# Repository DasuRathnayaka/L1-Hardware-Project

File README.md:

# Automated Camera Stand
## What is this?
This is an Automated camera stand which possible to guide using GPS coordinates with an obstacle avoidance navigation system. This is made to help wildlife photographers to take good photographs in insecure environments.

## Why is this?
We mainly focused on avoiding danger for the wildlife photographer and the safety of the camera. In this period many wildlife photographers are facing danger while taking photos due to animal attacks. We are going to introduce a new device to avoid such a problem.

## 3D Model

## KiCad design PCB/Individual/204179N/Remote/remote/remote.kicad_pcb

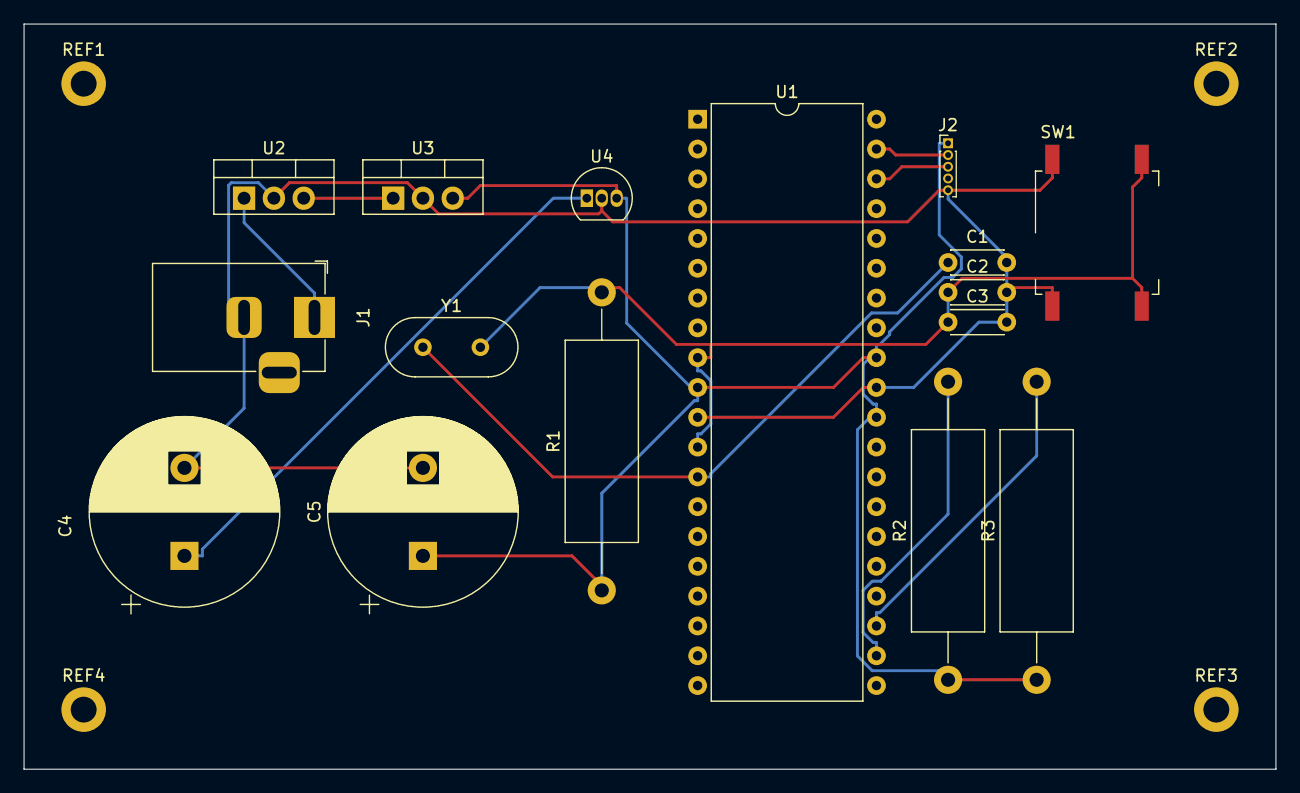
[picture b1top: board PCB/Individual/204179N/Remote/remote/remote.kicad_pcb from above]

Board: 2 copper layers, 106.7 x 63.5 mm, 20 parts (0 on the bottom side), 11 nets.

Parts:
C1, C2: 22pF; C_Disc_D4.3mm_W1.9mm_P5.00mm
C3: 10uF; C_Disc_D4.3mm_W1.9mm_P5.00mm
C4, C5: 470uF; CP_Radial_D16.0mm_P7.50mm
J1: Barrel_Jack; BarrelJack_Horizontal
J2: Joystick (Motor); PinHeader_1x05_P1.00mm_Vertical
R1: 10k; R_Axial_DIN0617_L17.0mm_D6.0mm_P25.40mm_Horizontal
R2, R3: 4.7k; R_Axial_DIN0617_L17.0mm_D6.0mm_P25.40mm_Horizontal
REF1: M1; MountingHole_2.2mm_M2_ISO14580_Pad
REF2: M2; MountingHole_2.2mm_M2_ISO14580_Pad
REF3: M3; MountingHole_2.2mm_M2_ISO14580_Pad
REF4: M4; MountingHole_2.2mm_M2_ISO14580_Pad
SW1: Reset Button; SW_MEC_5GSH9
U1: ATmega32-16P; DIP-40_W15.24mm
U2: L7809; TO-220-3_Vertical
U3: L7805; TO-220-3_Vertical
U4: L78L33_TO92; TO-92_Inline
Y1: Crystal; Crystal_HC18-U_Vertical

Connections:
/Atmega32/5V: C5.1, J2.1 (5V), R1.1, R2.1, R3.1, U1.10 (VCC), U1.30 (AVCC), U1.32 (AREF), U3.3 (OUT), U4.3 (VI)
/Atmega32/A1: J2.2 (VRx), U1.39 (PA1)
/Atmega32/A2: J2.3 (VRy), U1.38 (PA2)
/Atmega32/GND: C1.2, C2.2, C3.2, C4.2, C5.2, J1.2, J2.5 (GND), SW1.1 (A), SW1.2 (A), U1.11 (GND), U1.31 (GND), U2.2 (GND), U3.2 (GND), U4.2 (GND)
/Atmega32/SCL: R2.2, U1.22 (PC0)
/Atmega32/SDA: R3.2, U1.23 (PC1)
/Power Supply/3.3V: C4.1, U4.1 (VO)
/Power Supply/12V: J1.1, U2.1 (IN)
unnamed: C1.1, U1.13 (XTAL1), Y1.1
unnamed: C2.1, C3.1, R1.2, SW1.3 (B), SW1.4 (B), U1.9 (~RESET), U1.12 (XTAL2), Y1.2
unnamed: U2.3 (OUT), U3.1 (IN)

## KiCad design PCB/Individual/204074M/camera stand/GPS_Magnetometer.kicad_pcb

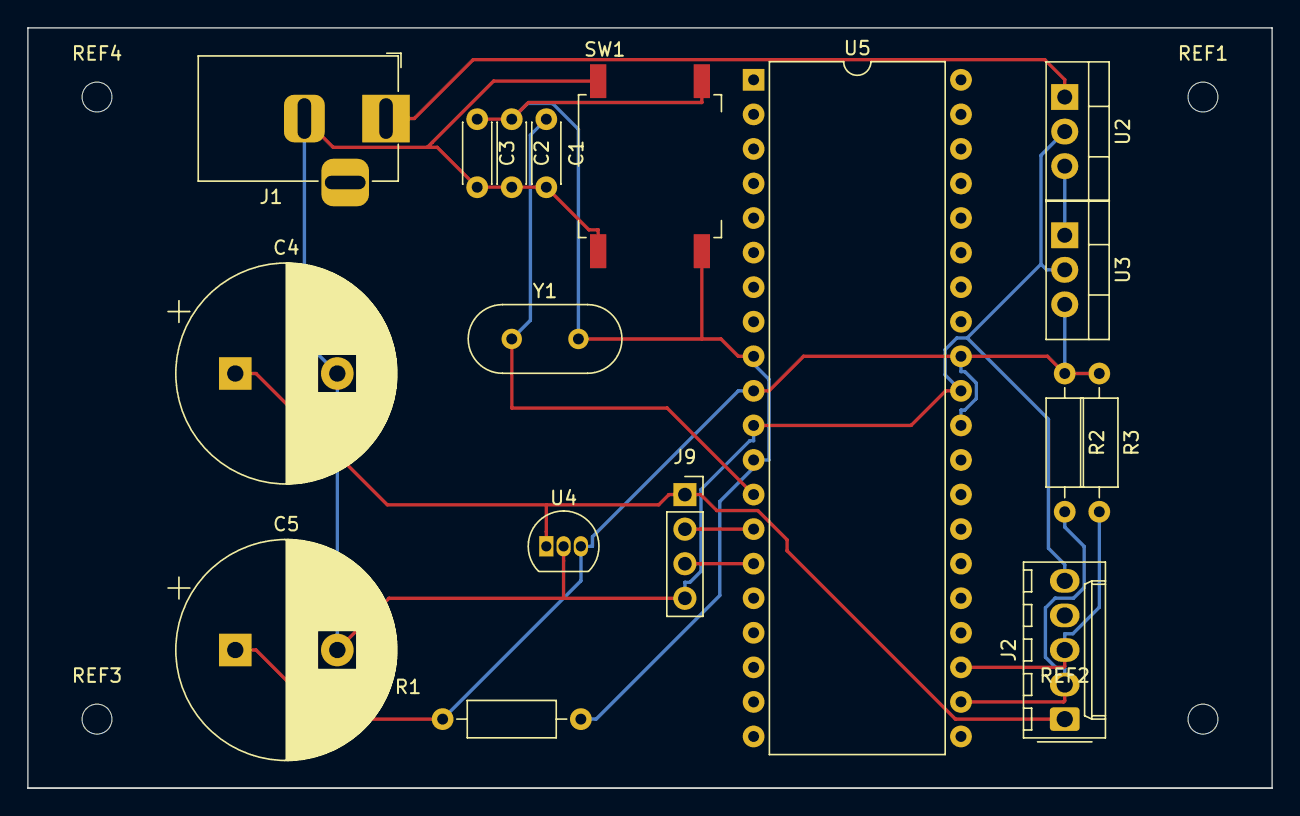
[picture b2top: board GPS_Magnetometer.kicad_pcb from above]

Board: 2 copper layers, 91.4 x 55.9 mm, 21 parts (0 on the bottom side), 11 nets.

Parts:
C1, C2: 22pF; C_Disc_D4.3mm_W1.9mm_P5.00mm
C3: 10uF; C_Disc_D4.3mm_W1.9mm_P5.00mm
C4, C5: 470uF; CP_Radial_D16.0mm_P7.50mm
J1: Barrel_Jack; BarrelJack_Horizontal
J2: HMC5883L; Molex_KK-254_AE-6410-05A_1x05_P2.54mm_Vertical
J9: GPS Module; PinSocket_1x04_P2.54mm_Vertical
R1: 10k; R_Axial_DIN0207_L6.3mm_D2.5mm_P10.16mm_Horizontal
R2, R3: 4.7k; R_Axial_DIN0207_L6.3mm_D2.5mm_P10.16mm_Horizontal
REF1, REF2, REF3, REF4: MountingHole_2.2mm_M2
SW1: Reset Button; SW_MEC_5GSH9
U2: L7809; TO-220-3_Vertical
U3: L7805; TO-220-3_Vertical
U4: L78L33_TO92; TO-92_Inline
U5: ATmega32-16P; DIP-40_W15.24mm
Y1: Crystal; Crystal_HC18-U_Vertical

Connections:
/Atmega32/5V: C5.1, R1.1, R2.1, R3.1, U3.3 (OUT), U4.3 (VI), U5.10 (VCC), U5.30 (AVCC), U5.32 (AREF)
/Atmega32/GND: C1.2, C2.2, C3.2, C4.2, C5.2, J1.2, J2.5 (GND), J9.4 (GND), SW1.1 (A), SW1.2 (A), U2.2 (GND), U3.2 (GND), U4.2 (GND), U5.11 (GND), U5.31 (GND)
/Atmega32/Rx: J9.2 (Tx), U5.14 (PD0)
/Atmega32/SCL: J2.2 (SCL), R2.2, U5.22 (PC0)
/Atmega32/SDA: J2.3 (SDA), R3.2, U5.23 (PC1)
/Atmega32/Tx: J9.3 (Rx), U5.15 (PD1)
/Power Supply/3.3V: C4.1, J2.1 (VCC), J9.1 (VCC), U4.1 (VO)
/Power Supply/12V: J1.1, U2.1 (IN)
unnamed: C1.1, U5.13 (XTAL1), Y1.1
unnamed: C2.1, C3.1, R1.2, SW1.3 (B), SW1.4 (B), U5.9 (~RESET), U5.12 (XTAL2), Y1.2
unnamed: U2.3 (OUT), U3.1 (IN)

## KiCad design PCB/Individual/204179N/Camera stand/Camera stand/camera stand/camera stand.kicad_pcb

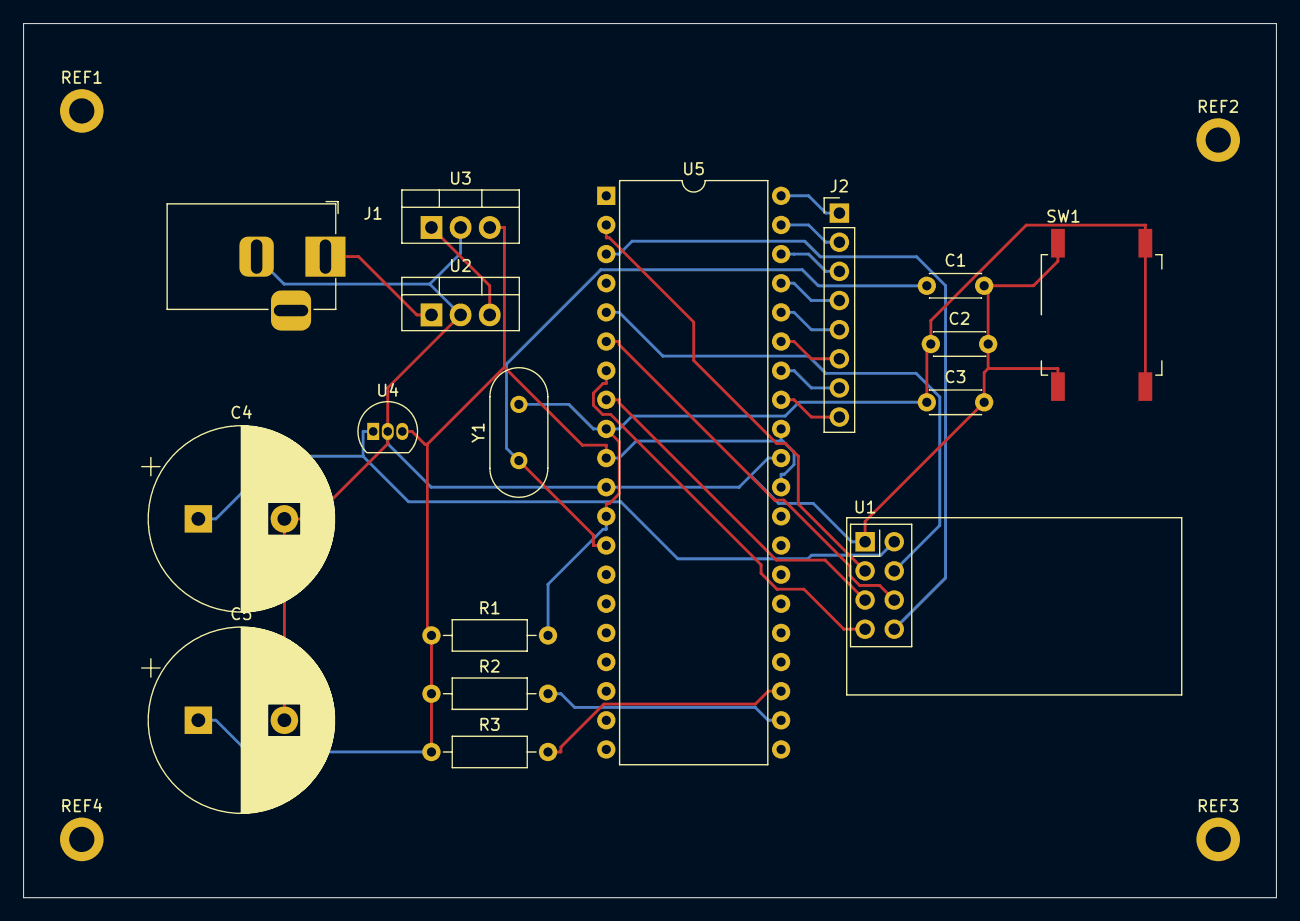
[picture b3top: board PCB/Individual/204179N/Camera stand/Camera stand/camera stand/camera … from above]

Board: 2 copper layers, 109.2 x 76.2 mm, 21 parts (0 on the bottom side), 23 nets.

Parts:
C1, C2: 22pF; C_Disc_D4.3mm_W1.9mm_P5.00mm
C3: 10uF; C_Disc_D4.3mm_W1.9mm_P5.00mm
C4, C5: 470uF; CP_Radial_D16.0mm_P7.50mm
J1: Barrel_Jack; BarrelJack_Horizontal
J2: Keypad 4x4; PinHeader_1x08_P2.54mm_Vertical
R1: 10k; R_Axial_DIN0207_L6.3mm_D2.5mm_P10.16mm_Horizontal
R2, R3: 4.7k; R_Axial_DIN0207_L6.3mm_D2.5mm_P10.16mm_Horizontal
REF1: M1; MountingHole_2.2mm_M2_ISO14580_Pad
REF2: M2; MountingHole_2.2mm_M2_ISO14580_Pad
REF3: M3; MountingHole_2.2mm_M2_ISO14580_Pad
REF4: M4; MountingHole_2.2mm_M2_ISO14580_Pad
SW1: Reset Button; SW_MEC_5GSH9
U1: NRF24L01; nRF24L01_Breakout
U2: L7809; TO-220-3_Vertical
U3: L7805; TO-220-3_Vertical
U4: L78L33_TO92; TO-92_Inline
U5: ATmega32-16P; DIP-40_W15.24mm
Y1: Crystal; Crystal_HC18-U_Vertical

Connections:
/Atmega32/5V: C5.1, R1.1, R2.1, R3.1, U3.3 (OUT), U4.3 (VI), U5.10 (VCC), U5.30 (AVCC), U5.32 (AREF)
/Atmega32/A0: J2.1 (Col_A), U5.40 (PA0)
/Atmega32/A1: J2.2 (Col_B), U5.39 (PA1)
/Atmega32/A2: J2.3 (Col_C), U5.38 (PA2)
/Atmega32/A3: J2.4 (Col_D), U5.37 (PA3)
/Atmega32/A4: J2.5 (Row_1), U5.36 (PA4)
/Atmega32/A5: J2.6 (Row_2), U5.35 (PA5)
/Atmega32/A6: J2.7 (Row_3), U5.34 (PA6)
/Atmega32/A7: J2.8 (Row_4), U5.33 (PA7)
/Atmega32/CE: U1.3 (CE), U5.2 (PB1)
/Atmega32/CSN: U1.4 (~CSN), U5.5 (PB4)
/Atmega32/GND: C1.2, C2.2, C3.2, C4.2, C5.2, J1.2, SW1.1 (A), SW1.2 (A), U1.1 (GND), U2.2 (GND), U3.2 (GND), U4.2 (GND), U5.11 (GND), U5.31 (GND)
/Atmega32/IRQ: U1.8 (IRQ), U5.3 (PB2)
/Atmega32/MISO: U1.7 (MISO), U5.7 (PB6)
/Atmega32/MOSI: U1.6 (MOSI), U5.6 (PB5)
/Atmega32/SCK: U1.5 (SCK), U5.8 (PB7)
/Atmega32/SCL: R2.2, U5.22 (PC0)
/Atmega32/SDA: R3.2, U5.23 (PC1)
/Power Supply/3.3V: C4.1, U1.2 (VCC), U4.1 (VO)
/Power Supply/12V: J1.1, U2.1 (IN)
unnamed: C1.1, U5.13 (XTAL1), Y1.1
unnamed: C2.1, C3.1, R1.2, SW1.3 (B), SW1.4 (B), U5.9 (~RESET), U5.12 (XTAL2), Y1.2
unnamed: U2.3 (OUT), U3.1 (IN)

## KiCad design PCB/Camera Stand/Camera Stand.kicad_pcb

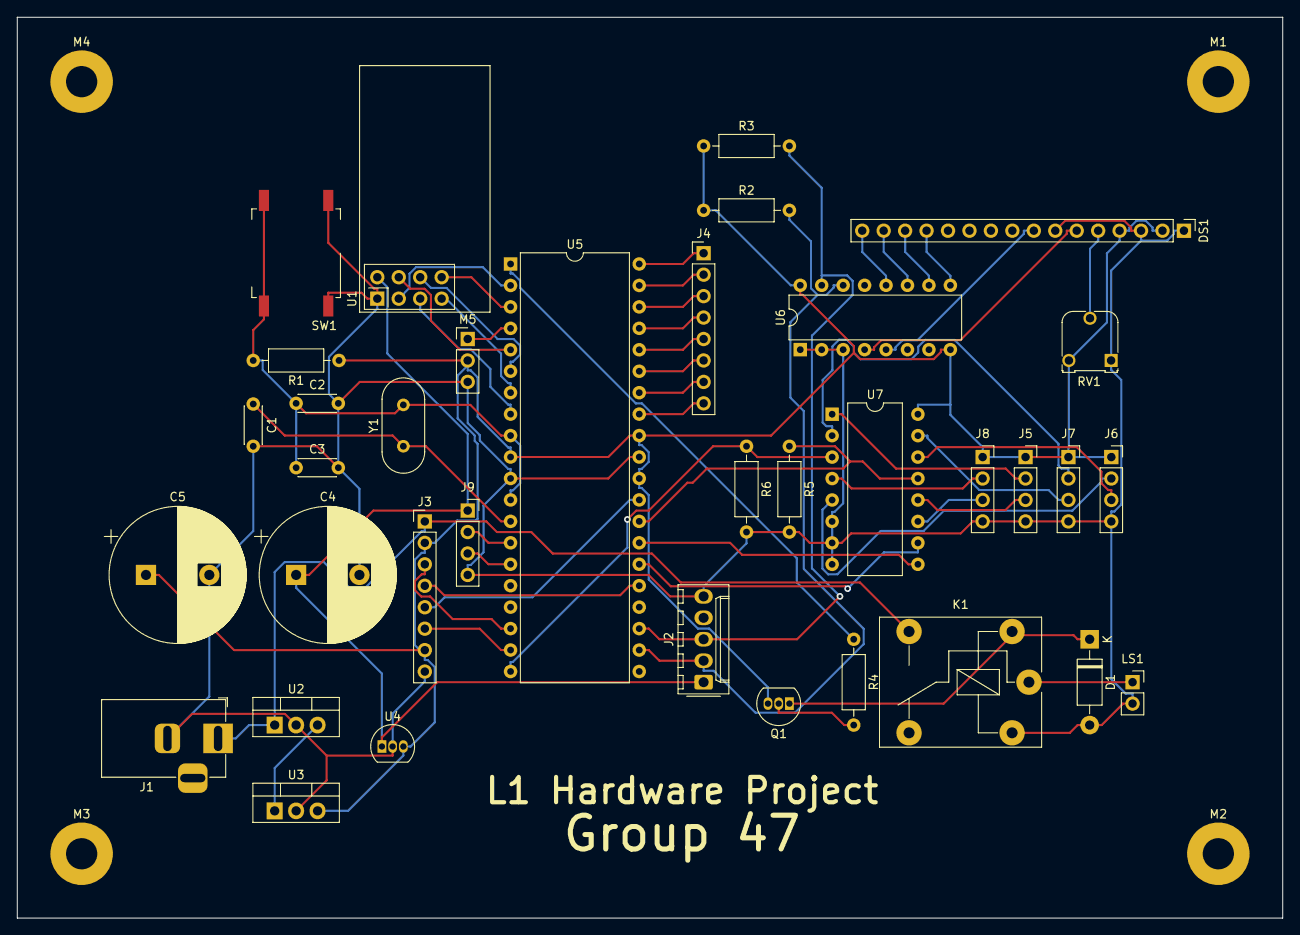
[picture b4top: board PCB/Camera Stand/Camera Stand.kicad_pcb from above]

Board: 2 copper layers, 149.9 x 106.7 mm, 40 parts (0 on the bottom side), 53 nets.

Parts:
C1, C2: 22pF; C_Disc_D4.3mm_W1.9mm_P5.00mm
C3: 10uF; C_Disc_D4.3mm_W1.9mm_P5.00mm
C4, C5: 470uF; CP_Radial_D16.0mm_P7.50mm
D1: 1N4007; D_DO-41_SOD81_P10.16mm_Horizontal
DS1: HY1602E; PinHeader_1x16_P2.54mm_Vertical
J1: Barrel_Jack; BarrelJack_Horizontal
J2: HMC5883L; Molex_KK-254_AE-6410-05A_1x05_P2.54mm_Vertical
J3: Motor Drive; PinHeader_1x08_P2.54mm_Vertical
J4: Keypad 4x4; PinHeader_1x08_P2.54mm_Vertical
J5: Ultrasonic Left Front; PinSocket_1x04_P2.54mm_Vertical
J6: Ultrasonic Right Front; PinSocket_1x04_P2.54mm_Vertical
J7: Ultrasonic Left Back; PinSocket_1x04_P2.54mm_Vertical
J8: Ultrasonic Right Back; PinSocket_1x04_P2.54mm_Vertical
J9: GPS Module; PinSocket_1x04_P2.54mm_Vertical
K1: Relay; Relay_SPDT_Finder_36.11
LS1: Speaker; PinSocket_1x02_P2.54mm_Vertical
M1, M2, M3, M4: MountingHole_3.7mm_Pad
M5: Motor_Servo; PinHeader_1x03_P2.54mm_Vertical
Q1: PN2222A; TO-92_Inline
R1, R5, R6: 10k; R_Axial_DIN0207_L6.3mm_D2.5mm_P10.16mm_Horizontal
R2, R3: 4.7k; R_Axial_DIN0207_L6.3mm_D2.5mm_P10.16mm_Horizontal
R4: 100k; R_Axial_DIN0207_L6.3mm_D2.5mm_P10.16mm_Horizontal
RV1: Potentiometer; Potentiometer_Runtron_RM-065_Vertical
SW1: Reset Button; SW_MEC_5GSH9
U1: NRF24L01; nRF24L01_Breakout
U2: L7809; TO-220-3_Vertical
U3: L7805; TO-220-3_Vertical
U4: L78L33_TO92; TO-92_Inline
U5: ATmega32-16P; DIP-40_W15.24mm
U6: PCF8574A; DIP-16_W7.62mm
U7: CD4052B; DIP-16_W10.16mm
Y1: Crystal; Crystal_HC18-U_Vertical

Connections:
/Atmega32/5V: C5.1, DS1.2 (LEDA), DS1.4 (VDD), J3.2 (ENA), J3.7 (ENB), J5.1 (VCC), J6.1 (VCC), J7.1 (VCC), J8.1 (VCC), M5.2 (+), Q1.3 (C), R1.1, R2.1, R3.1, RV1.3, U3.3 (OUT), U4.3 (VI), U5.10 (VCC), U5.30 (AVCC), U5.32 (AREF), U6.8 (VSS), U6.16 (VDD), U7.16 (VDD)
/Atmega32/A0: J4.1 (Col_A), U5.40 (PA0)
/Atmega32/A1: J4.2 (Col_B), U5.39 (PA1)
/Atmega32/A2: J4.3 (Col_C), U5.38 (PA2)
/Atmega32/A3: J4.4 (Col_D), U5.37 (PA3)
/Atmega32/A4: J4.5 (Row_1), U5.36 (PA4)
/Atmega32/A5: J4.6 (Row_2), U5.35 (PA5)
/Atmega32/A6: J4.7 (Row_3), U5.34 (PA6)
/Atmega32/A7: J4.8 (Row_4), U5.33 (PA7)
/Atmega32/B0: R4.1, U5.1 (PB0)
/Atmega32/B3: M5.1 (PWM), U5.4 (PB3)
/Atmega32/C3: J3.4 (INA2), U5.25 (PC3)
/Atmega32/C4: U5.26 (PC4), U7.10 (A)
/Atmega32/C5: U5.27 (PC5), U7.9 (B)
/Atmega32/C6: R5.1, U5.28 (PC6), U7.13 (X)
/Atmega32/C7: J3.5 (INB1), U5.29 (PC7)
/Atmega32/CE: U1.3 (CE), U5.2 (PB1)
/Atmega32/CSN: U1.4 (~CSN), U5.5 (PB4)
/Atmega32/D4: J3.3 (INA1), U5.18 (PD4)
/Atmega32/D5: J3.6 (INB2), U5.19 (PD5)
/Atmega32/D6: R6.1, U5.20 (PD6), U7.3 (Y)
/Atmega32/GND: C1.2, C2.2, C3.2, C4.2, C5.2, D1.2 (A), DS1.1 (LEDK), DS1.3 (VSS), DS1.7 (R/~W), J1.2, J2.5 (GND), J3.8 (GND), J5.4 (GND), J6.4 (GND), J7.4 (GND), J8.4 (GND), J9.4 (GND), K1.A2, LS1.2, M5.3 (-), R5.2, R6.2, RV1.1, SW1.1 (A), SW1.2 (A), U1.1 (GND), U2.2 (GND), U3.2 (GND), U4.2 (GND), U5.11 (GND), U5.31 (GND), U6.1 (A0), U6.2 (A1), U6.3 (A2), U7.6 (INH), U7.7 (VEE), U7.8 (VSS)
/Atmega32/IRQ: U1.8 (IRQ), U5.3 (PB2)
/Atmega32/MISO: U1.7 (MISO), U5.7 (PB6)
/Atmega32/MOSI: U1.6 (MOSI), U5.6 (PB5)
/Atmega32/Rx: J9.2 (Tx), U5.14 (PD0)
/Atmega32/SCK: U1.5 (SCK), U5.8 (PB7)
/Atmega32/SCL: J2.2 (SCL), R2.2, U5.22 (PC0), U6.14 (SCL)
/Atmega32/SDA: J2.3 (SDA), R3.2, U5.23 (PC1), U6.15 (SDA)
/Atmega32/Tx: J9.3 (Rx), U5.15 (PD1)
/Power Supply/3.3V: C4.1, J2.1 (VCC), J9.1 (VCC), U1.2 (VCC), U4.1 (VO)
/Power Supply/12V: J1.1, J3.1 (VCC), K1.14, U2.1 (IN)
unnamed: C1.1, U5.13 (XTAL1), Y1.1
unnamed: C2.1, C3.1, R1.2, SW1.3 (B), SW1.4 (B), U5.9 (~RESET), U5.12 (XTAL2), Y1.2
unnamed: D1.1 (K), K1.A1, Q1.1 (E)
unnamed: DS1.5 (Vo), RV1.2
unnamed: DS1.6 (RS), U6.4 (P0)
unnamed: DS1.8 (E), U6.5 (P1)
unnamed: DS1.13 (DB4), U6.9 (P4)
unnamed: DS1.14 (DB5), U6.10 (P5)
unnamed: DS1.15 (DB6), U6.11 (P6)
unnamed: DS1.16 (DB7), U6.12 (P7)
unnamed: J5.2 (Echo), U7.1 (Y0)
unnamed: J5.3 (Trig), U7.12 (X0)
unnamed: J6.2 (Echo), U7.5 (Y1)
unnamed: J6.3 (Trig), U7.14 (X1)
unnamed: J7.2 (Echo), U7.2 (Y2)
unnamed: J7.3 (Trig), U7.15 (X2)
unnamed: J8.2 (Echo), U7.4 (Y3)
unnamed: J8.3 (Trig), U7.11 (X3)
unnamed: K1.11, LS1.1
unnamed: Q1.2 (B), R4.2
unnamed: U2.3 (OUT), U3.1 (IN)

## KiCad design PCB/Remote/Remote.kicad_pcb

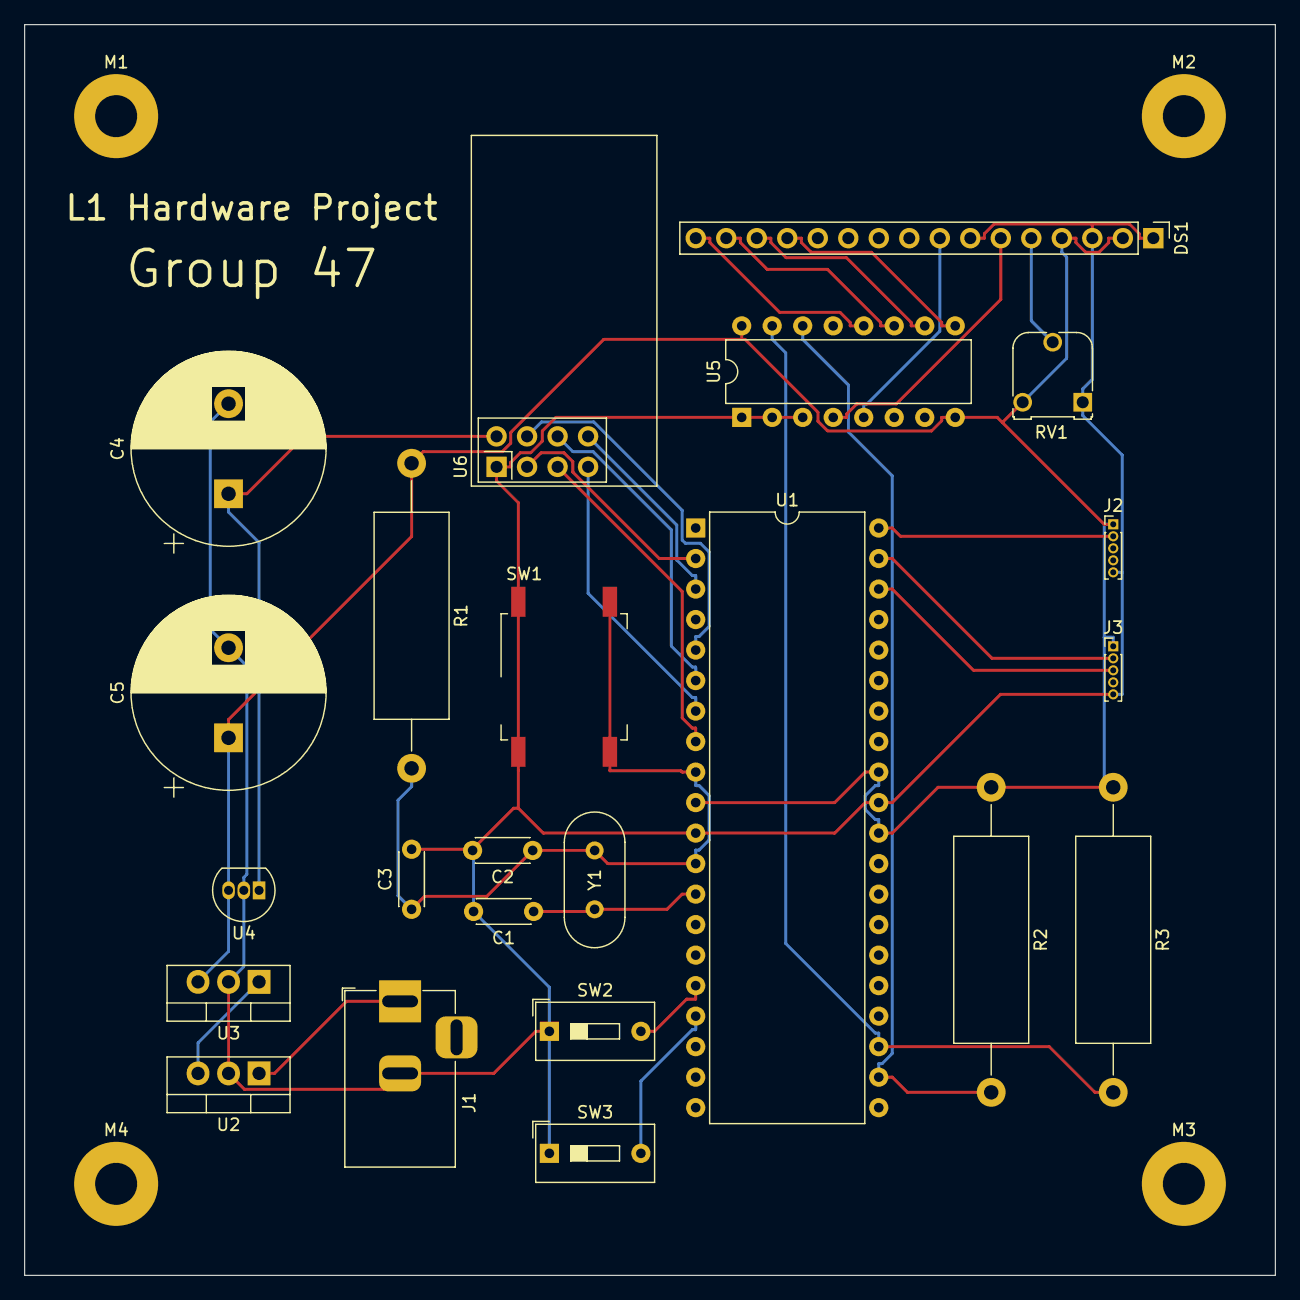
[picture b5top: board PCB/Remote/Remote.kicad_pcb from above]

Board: 2 copper layers, 104.1 x 104.1 mm, 27 parts (0 on the bottom side), 27 nets.

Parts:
C1, C2: 22pF; C_Disc_D4.3mm_W1.9mm_P5.00mm
C3: 10uF; C_Disc_D4.3mm_W1.9mm_P5.00mm
C4, C5: 470uF; CP_Radial_D16.0mm_P7.50mm
DS1: HY1602E; PinHeader_1x16_P2.54mm_Vertical
J1: Barrel_Jack; BarrelJack_Horizontal
J2: Joystick (Servo); PinHeader_1x05_P1.00mm_Vertical
J3: Joystick (Motor); PinHeader_1x05_P1.00mm_Vertical
M1, M2, M3, M4: MountingHole_3.5mm_Pad
R1: 10k; R_Axial_DIN0617_L17.0mm_D6.0mm_P25.40mm_Horizontal
R2, R3: 4.7k; R_Axial_DIN0617_L17.0mm_D6.0mm_P25.40mm_Horizontal
RV1: Potentiometer; Potentiometer_Runtron_RM-065_Vertical
SW1: Reset Button; SW_MEC_5GSH9
SW2: Auto/Manual; SW_DIP_SPSTx01_Slide_9.78x4.72mm_W7.62mm_P2.54mm
SW3: Siren on/off; SW_DIP_SPSTx01_Slide_9.78x4.72mm_W7.62mm_P2.54mm
U1: ATmega32-16P; DIP-40_W15.24mm
U2: L7809; TO-220-3_Vertical
U3: L7805; TO-220-3_Vertical
U4: L78L33_TO92; TO-92_Inline
U5: PCF8574A; DIP-16_W7.62mm
U6: NRF24L01; nRF24L01_Breakout
Y1: Crystal; Crystal_HC18-U_Vertical

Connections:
/Atmega32/5V: C5.1, DS1.2 (LEDA), DS1.4 (VDD), J2.1 (5V), J3.1 (5V), R1.1, R2.1, R3.1, RV1.3, U1.10 (VCC), U1.30 (AVCC), U1.32 (AREF), U3.3 (OUT), U4.3 (VI), U5.8 (VSS), U5.16 (VDD)
/Atmega32/A0: J2.2 (VRx), U1.40 (PA0)
/Atmega32/A1: J3.2 (VRx), U1.39 (PA1)
/Atmega32/A2: J3.3 (VRy), U1.38 (PA2)
/Atmega32/CE: U1.2 (PB1), U6.3 (CE)
/Atmega32/CSN: U1.5 (PB4), U6.4 (~CSN)
/Atmega32/D2: SW2.2 (B), U1.16 (PD2)
/Atmega32/D3: SW3.2 (B), U1.17 (PD3)
/Atmega32/GND: C1.2, C2.2, C3.2, C4.2, C5.2, DS1.1 (LEDK), DS1.3 (VSS), DS1.7 (R/~W), J1.2, J2.5 (GND), J3.5 (GND), RV1.1, SW1.1 (A), SW1.2 (A), SW2.1 (A), SW3.1 (A), U1.11 (GND), U1.31 (GND), U2.2 (GND), U3.2 (GND), U4.2 (GND), U5.1 (A0), U5.2 (A1), U5.3 (A2), U6.1 (GND)
/Atmega32/IRQ: U1.3 (PB2), U6.8 (IRQ)
/Atmega32/MISO: U1.7 (PB6), U6.7 (MISO)
/Atmega32/MOSI: U1.6 (PB5), U6.6 (MOSI)
/Atmega32/SCK: U1.8 (PB7), U6.5 (SCK)
/Atmega32/SCL: R2.2, U1.22 (PC0), U5.14 (SCL)
/Atmega32/SDA: R3.2, U1.23 (PC1), U5.15 (SDA)
/Power Supply/3.3V: C4.1, U4.1 (VO), U6.2 (VCC)
/Power Supply/12V: J1.1, U2.1 (IN)
unnamed: C1.1, U1.13 (XTAL1), Y1.1
unnamed: C2.1, C3.1, R1.2, SW1.3 (B), SW1.4 (B), U1.9 (~RESET), U1.12 (XTAL2), Y1.2
unnamed: DS1.5 (Vo), RV1.2
unnamed: DS1.6 (RS), U5.4 (P0)
unnamed: DS1.8 (E), U5.5 (P1)
unnamed: DS1.13 (DB4), U5.9 (P4)
unnamed: DS1.14 (DB5), U5.10 (P5)
unnamed: DS1.15 (DB6), U5.11 (P6)
unnamed: DS1.16 (DB7), U5.12 (P7)
unnamed: U2.3 (OUT), U3.1 (IN)

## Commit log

2021-10-19 Basic block diagram
2021-10-20 Implementing base of the project.
2021-10-20 Add digital read function
2021-10-23 Create Resources.readme
    In this readme file we will be adding the resources need to continue the project.
2021-10-23 Update Resources.readme
    Added youtube link -ADC testing with proteus
2021-10-27 ADC reading.
2021-10-31 PWM readings
2021-11-19 Change folder architecture.
2021-11-30 Add documents and testing codes
2021-12-02 created a new branch
2021-12-02 add system diagram for interim
2021-12-03 Added the USART.c file
2021-12-03 made the circuit diagram
2021-12-04 Added discription to USART.c
2021-12-04 Added the GPS.c file and functions
2021-12-04 New circuit designs.
2021-12-04 changed the USART.c constant
2022-05-08 I started the proj
2022-05-09 Add keyboard.c and other some minor changes.
2022-05-10 chenged the protius file
2022-05-10 new protius diagram
2022-05-10 add SPI_Slave
2022-05-10 add SPI Master
2022-05-10 Add Slave and Master Separately
2022-05-11 Add I2C
2022-05-11 GPS module code
2022-05-11 Testing on SPI
2022-05-11 fixed SPI issue
2022-05-11 Minor changes
2022-05-12 SPI Update
2022-05-12 Merge
2022-05-13 magnetometer, GPS modified
2022-05-13 need protius file
2022-05-13 Changes in I2C
2022-05-13 nRF24L01 code
2022-05-15 Ended the project before finalize
2022-05-16 nRF modification
2022-05-17 Added the GPS code
2022-05-18 motor init
2022-05-18 Working GPS not needed way
2022-05-18 wording in GPS with display
2022-05-19 tried to chenged the GPS-not working
2022-05-19 GPS_init working
2022-05-20 Mater is completed.
2022-05-21 Finalized the GPS code
2022-05-21 Slave
2022-05-21 Add comments
2022-05-22 changed simply
2022-05-22 Proteus changes
2022-05-22 modified system diagram
2022-05-22 bot fix
2022-05-22 Interim scripts and report added
2022-05-22 changed comments
2022-05-22 Changed the comments
2022-05-22 Proteus file changes.
2022-05-22 finalized gps, magnet in slave
2022-05-23 changed a line
2022-05-23 changed the date of a file
2022-05-23 Individual codes.
2022-05-24 changed
2022-05-24 Add individual protues files
2022-05-25 add project sript 5/25
2022-06-05 Individual changes.
2022-06-06 Add PCB
2022-06-07 3.3v error in PCB
2022-06-07 12v to siren
2022-06-07 Individual PCB
2022-06-08 Added new System Diagram pdf
2022-06-08 Add individual PCB 204047J
2022-06-08 Add 204179N Individual pcb
2022-06-08 added the 204074M PCB
2022-06-08 added the final doc files
2022-06-08 Add individual pcb 204150T
2022-06-08 Changed System Diagram
2022-06-08 Update Camera Holder PCB 204047J
2022-06-08 Add simulation
2022-06-08 magnetometer simulation
2022-06-08 Simulation for button
2022-06-09 Add nrf simulation
2022-06-09 simualtion changes
2022-07-30 Update magnetometer.c
    Remove unwanted code part.
2022-07-30 final report
